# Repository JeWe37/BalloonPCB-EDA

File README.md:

# BalloonPCB-EDA

KiCAD EDA Files for the Balloon PCB.

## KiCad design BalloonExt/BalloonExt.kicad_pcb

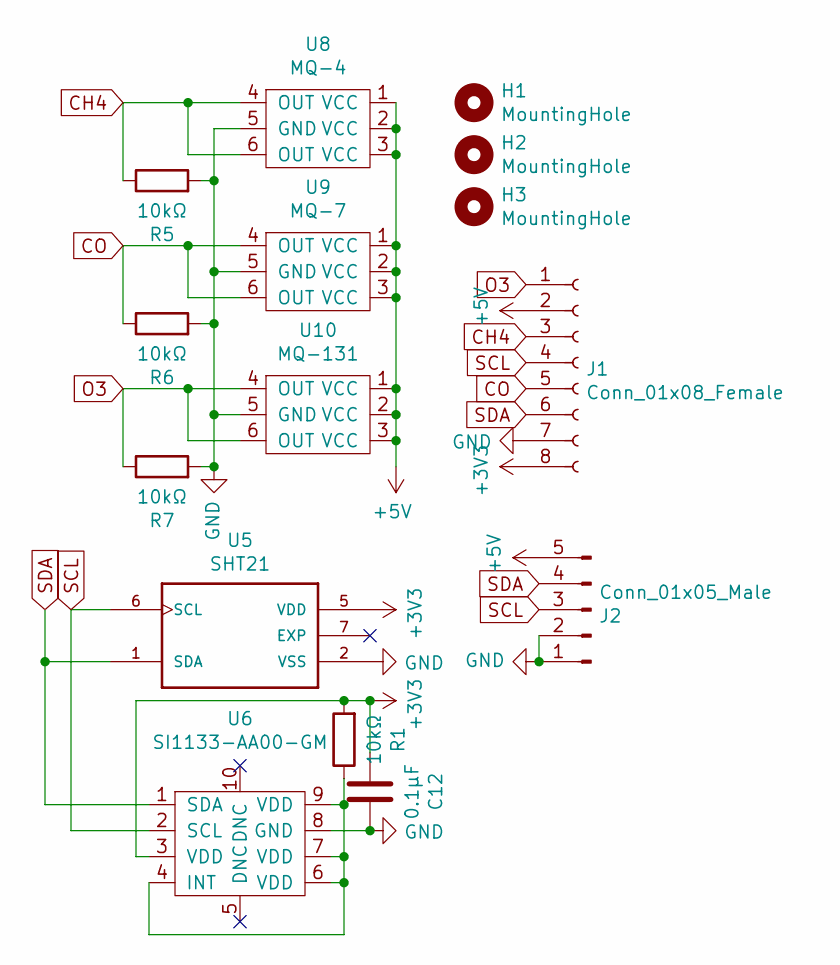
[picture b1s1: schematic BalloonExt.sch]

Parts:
C12: 0.1µF; C_0805_2012Metric
H1, H2, H3: MountingHole; MountingSlot_2.7x1mm
J1: Conn_01x08_Female; PinHeader_2x04_P1.27mm_Vertical
J2: Conn_01x05_Male; B5B-ZR
R1, R5, R6, R7: 10kΩ; R_0805_2012Metric
U5: SHT21; SON100P300X300X110-7N
U6: SI1133-AA00-GM; si1132
U8: MQ-4; mq-4
U9: MQ-7; mq-7
U10: MQ-131; mq-131

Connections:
+3V3: C12.2, J1.8, R1.2, U5.5 (VDD), U6.3 (VDD)
+5V: J1.2, J2.5, U8.1 (VCC), U8.2 (VCC), U8.3 (VCC), U9.1 (VCC), U9.2 (VCC), U9.3 (VCC), U10.1 (VCC), U10.2 (VCC), U10.3 (VCC)
CH4: J1.3, R5.1, U8.4 (OUT), U8.6 (OUT)
CO: J1.5, R6.1, U9.4 (OUT), U9.6 (OUT)
GND: C12.1, J1.7, J2.1, J2.2, R5.2, R6.2, R7.2, U5.2 (VSS), U6.8 (GND), U8.5 (GND), U9.5 (GND), U10.5 (GND)
unnamed: R1.1, U6.4 (INT), U6.6 (VDD), U6.7 (VDD), U6.9 (VDD)
O3: J1.1, R7.1, U10.4 (OUT), U10.6 (OUT)
SCL: J1.4, J2.3, U5.6 (SCL), U6.2 (SCL)
SDA: J1.6, J2.4, U5.1 (SDA), U6.1 (SDA)

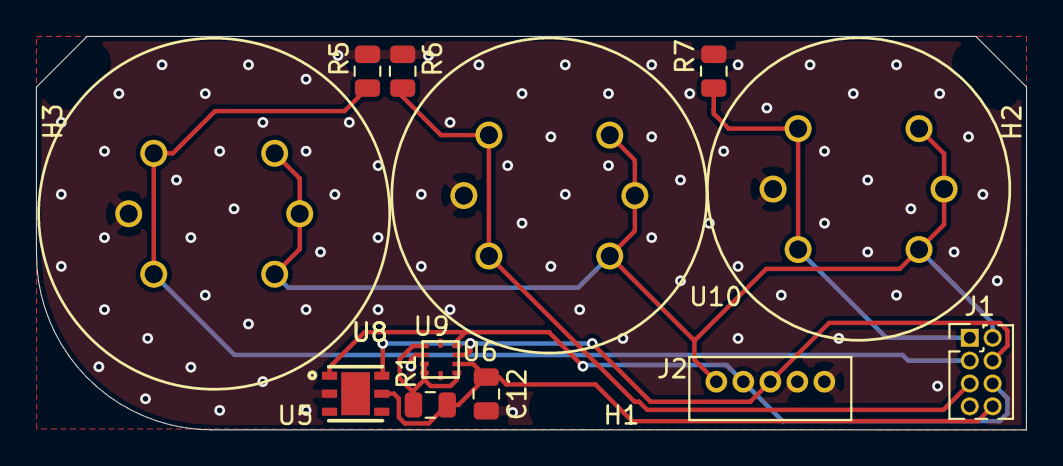
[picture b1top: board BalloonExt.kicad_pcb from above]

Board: 2 copper layers, 55.0 x 21.9 mm, 15 parts (0 on the bottom side), 9 nets.

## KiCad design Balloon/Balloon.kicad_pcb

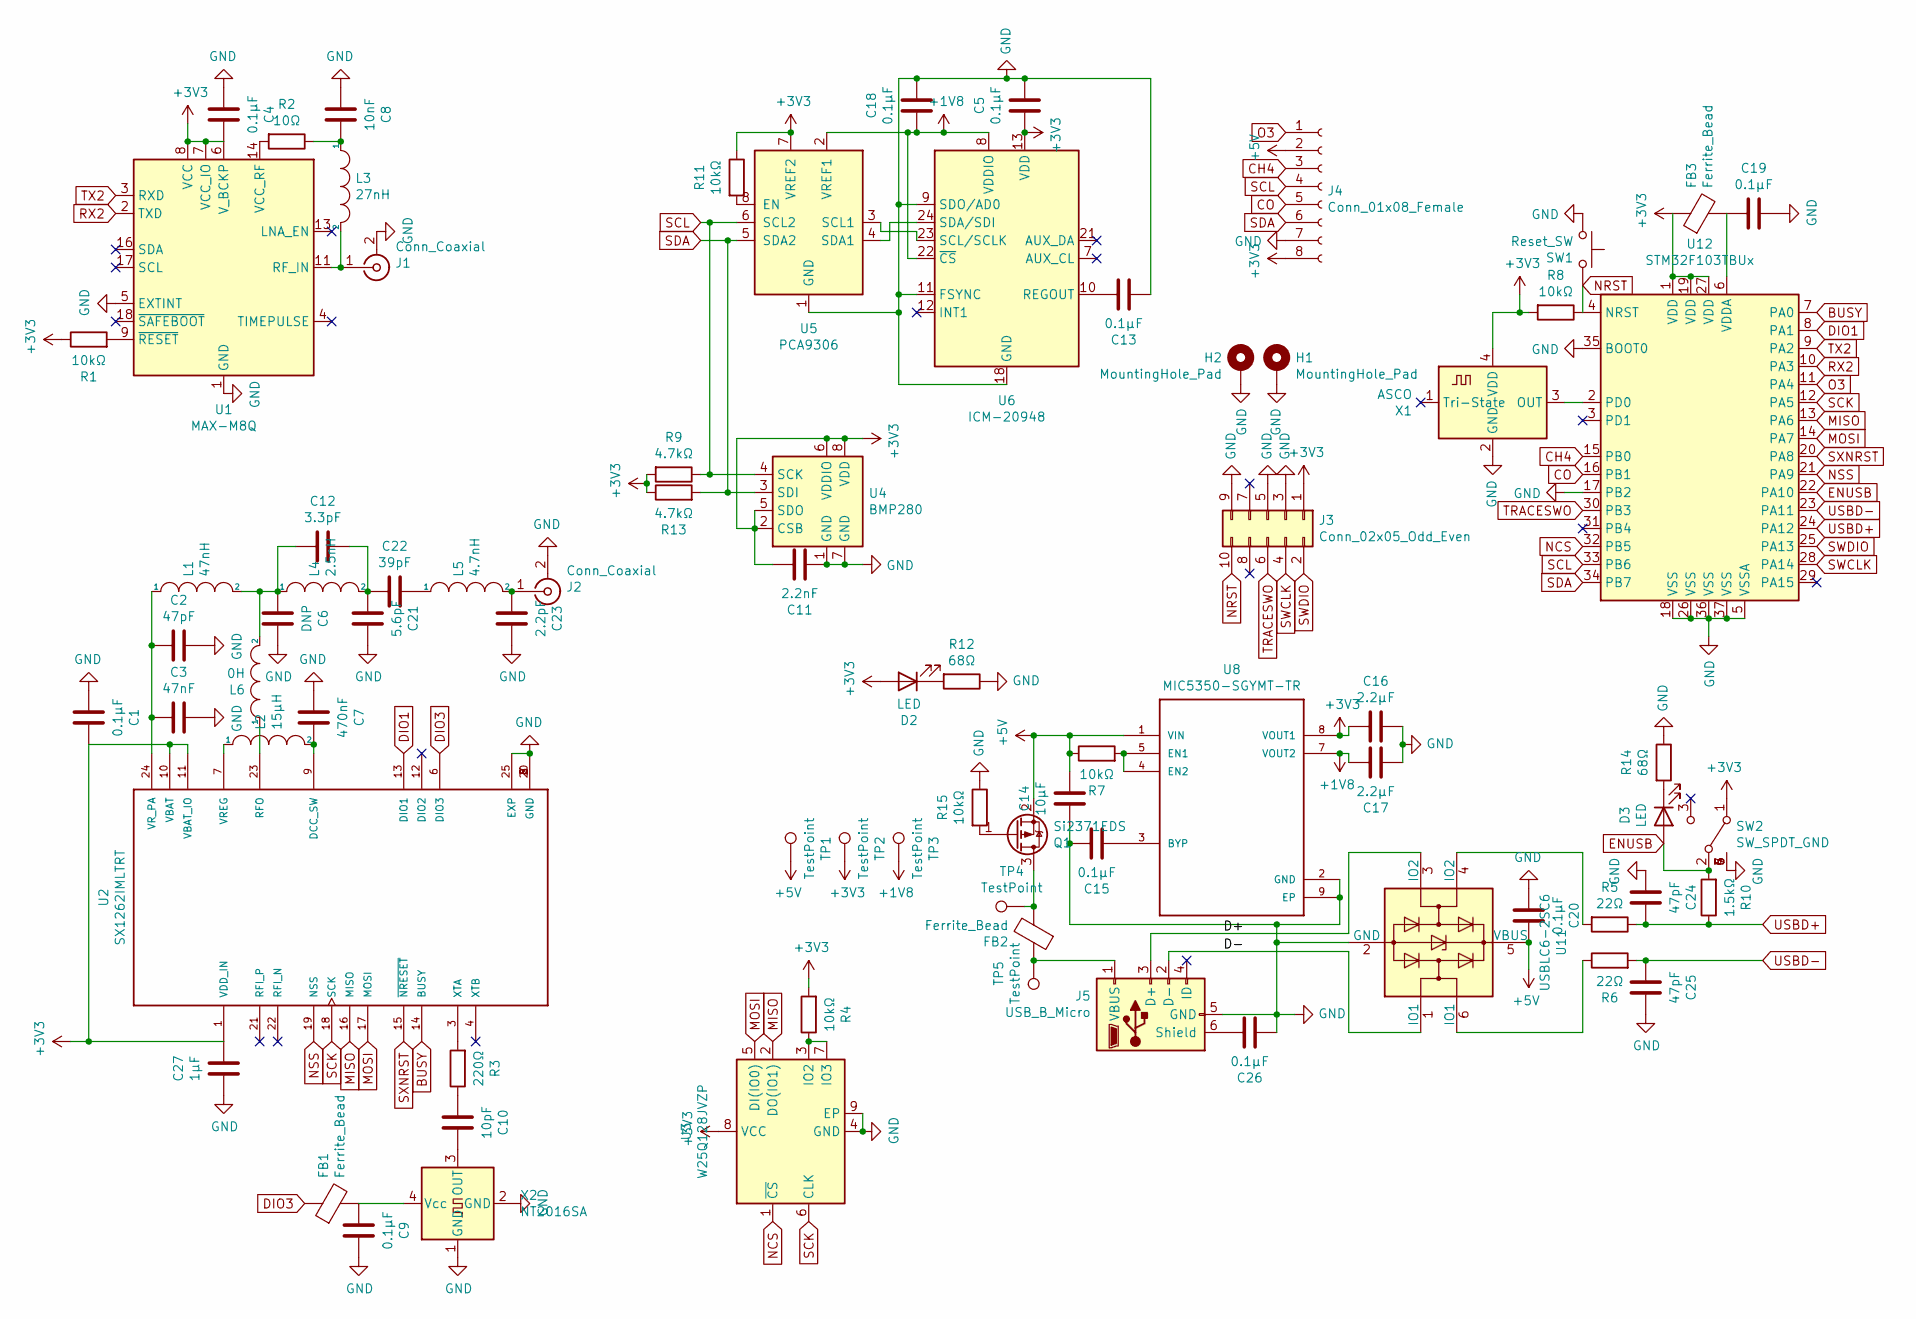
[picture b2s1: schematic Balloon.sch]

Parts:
C1, C4, C5, C9, C13, C15, C18, C19, C20, C26: 0.1µF; C_0201_0603Metric
C2, C24, C25: 47pF; C_0201_0603Metric
C3: 47nF; C_0201_0603Metric
C6: DNP; C_0201_0603Metric
C7: 470nF; C_0201_0603Metric
C8: 10nF; C_0201_0603Metric
C10: 10pF; C_0201_0603Metric
C11: 2.2nF; C_0201_0603Metric
C12: 3.3pF; C_0201_0603Metric
C14: 10µF; C_0603_1608Metric
C16, C17: 2.2µF; C_0402_1005Metric
C21: 5.6pF; C_0201_0603Metric
C22: 39pF; C_0201_0603Metric
C23: 2.2pF; C_0201_0603Metric
C27: 1µF; C_0402_1005Metric
D2, D3: LED; LED_0603_1608Metric
FB1, FB2, FB3: Ferrite_Bead; L_0402_1005Metric
H1, H2: MountingHole_Pad; MountingHole_2.2mm_M2_DIN965_Pad
J1: Conn_Coaxial; U.FL_Molex_MCRF_73412-0110_Vertical
J2: Conn_Coaxial; SMA_Amphenol_132289_EdgeMount
J3: Conn_02x05_Odd_Even; PinHeader_2x05_P1.27mm_Vertical
J4: Conn_01x08_Female; PinHeader_2x04_P1.27mm_Vertical
J5: USB_B_Micro; USB_Micro-B_Wuerth_629105150521
L1: 47nH; L_0201_0603Metric
L2: 15µH; L_0805_2021Metric_TDK
L3: 27nH; L_0201_0603Metric
L4: 2.5nH; L_0201_0603Metric
L5: 4.7nH; L_0201_0603Metric
L6: 0H; L_0201_0603Metric
Q1: Si2371EDS; SOT-23
R1, R4, R7, R8, R11, R15: 10kΩ; R_0201_0603Metric
R2: 10Ω; R_0201_0603Metric
R3: 220Ω; R_0201_0603Metric
R5, R6: 22Ω; R_0201_0603Metric
R9, R13: 4.7kΩ; R_0201_0603Metric
R10: 1.5kΩ; R_0201_0603Metric
R12, R14: 68Ω; R_0201_0603Metric
SW1: Reset_SW; SW_SPST_SKQG_WithStem
SW2: SW_SPDT_GND; SSSS811101
TP1, TP2, TP3, TP4, TP5: TestPoint; TestPoint_Pad_D2.5mm
U1: MAX-M8Q; ublox_MAX
U2: SX1262IMLTRT; QFN50P400X400X100-25N
U3: W25Q128JVZP; WSON-8-1EP_6x5mm_P1.27mm_EP3.4x4.3mm
U4: BMP280; Bosch_LGA-8_2x2.5mm_P0.65mm_ClockwisePinNumbering
U5: PCA9306; UQFN-8_1.6x1.6mm_P0.5mm
U6: ICM-20948; InvenSense_QFN-24_3x3mm_P0.4mm
U8: MIC5350-SGYMT-TR; SON50P200X200X60-9N
U11: USBLC6-2SC6; SOT-666
U12: STM32F103TBUx; QFN-36-1EP_6x6mm_P0.5mm_EP4.1x4.1mm
X1: ASCO; Oscillator_SMD_Abracon_ASCO-4Pin_1.6x1.2mm
X2: NT2016SA; SOIC254P1016X440-4N

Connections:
+1V8: C17.2, C18.2, TP3.1, U5.2 (VREF1), U6.8 (VDDIO), U6.22 (~CS), U8.7 (VOUT2); also elsewhere on the board
+5V: C14.1, C20.1, J4.2, Q1.2 (S), R7.1, TP1.1, U8.1 (VIN), U11.5 (VBUS); also elsewhere on the board
/D+: J5.3 (D+), U11.3 (IO2)
/D-: J5.2 (D-), U11.1 (IO1)
BUSY: U2.14 (BUSY), U12.7 (PA0)
CH4: J4.3, U12.15 (PB0)
CO: J4.5, U12.16 (PB1)
DIO1: U2.13 (DIO1), U12.8 (PA1)
DIO3: FB1.1, U2.6 (DIO3)
ENUSB: D3.2 (A), R10.2, SW2.2 (B), U12.22 (PA10)
MISO: U2.16 (MISO), U3.2 (DO(IO1)), U12.13 (PA6)
MOSI: U2.17 (MOSI), U3.5 (DI(IO0)), U12.14 (PA7)
NCS: U3.1 (~CS), U12.32 (PB5)
NRST: J3.10, R8.1, SW1.2, U12.4 (NRST)
NSS: U2.19 (NSS), U12.21 (PA9)
unnamed: C2.1, C3.1, L1.1, U2.24 (VR_PA)
unnamed: C7.1, L2.2, U2.9 (DCC_SW)
unnamed: C8.1, L3.1, R2.1
unnamed: C9.2, FB1.2, X2.4 (Vcc)
unnamed: C10.1, X2.3 (OUT)
unnamed: C10.2, R3.1
unnamed: C6.1, C12.1, L1.2, L4.1, L6.2
unnamed: C12.2, C21.1, C22.1, L4.2
unnamed: C13.1, U6.10 (REGOUT)
unnamed: C15.2, U8.3 (BYP)
unnamed: C19.2, FB3.2, U12.6 (VDDA)
unnamed: C22.2, L5.1
unnamed: C23.1, J2.1 (In), L5.2
unnamed: C26.1, J5.6 (Shield)
unnamed: D2.1 (K), R12.2
unnamed: D3.1 (K), R14.2
unnamed 31: FB2.1, J5.1 (VBUS), TP5.1; also elsewhere on the board
unnamed 32: FB2.2, Q1.3 (D), TP4.1; also elsewhere on the board
unnamed: J1.1 (In), L3.2, U1.11 (RF_IN)
unnamed: L2.1, U2.7 (VREG)
unnamed: L6.1, U2.23 (RFO)
unnamed: Q1.1 (G), R15.2
unnamed: R1.2, U1.9 (~RESET)
unnamed: R2.2, U1.14 (VCC_RF)
unnamed: R3.2, U2.3 (XTA)
unnamed: R4.1, U3.3 (IO2), U3.7 (IO3)
unnamed: R5.2, U11.4 (IO2)
unnamed: R6.1, U11.6 (IO1)
unnamed: R7.2, U8.4 (EN2), U8.5 (EN1)
unnamed: R11.2, U5.8 (EN)
unnamed: U5.3 (SCL1), U6.23 (SCL/SCLK)
unnamed: U5.4 (SDA1), U6.24 (SDA/SDI)
unnamed: U12.2 (PD0), X1.3 (OUT)
O3: J4.1, U12.11 (PA4)
RX2: U1.2 (TXD), U12.10 (PA3)
SCK: U2.18 (SCK), U3.6 (CLK), U12.12 (PA5)
SCL: J4.4, R9.1, U4.4 (SCK), U5.6 (SCL2), U12.33 (PB6)
SWCLK: J3.4, U12.28 (PA14)
SWDIO: J3.2, U12.25 (PA13)
SXNRST: U2.15 (~NRESET~), U12.20 (PA8)
TRACESWO: J3.6, U12.30 (PB3)
TX2: U1.3 (RXD), U12.9 (PA2)
USBD+: C24.1, R5.1, R10.1, U12.24 (PA12)
USBD-: C25.2, R6.2, U12.23 (PA11)

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
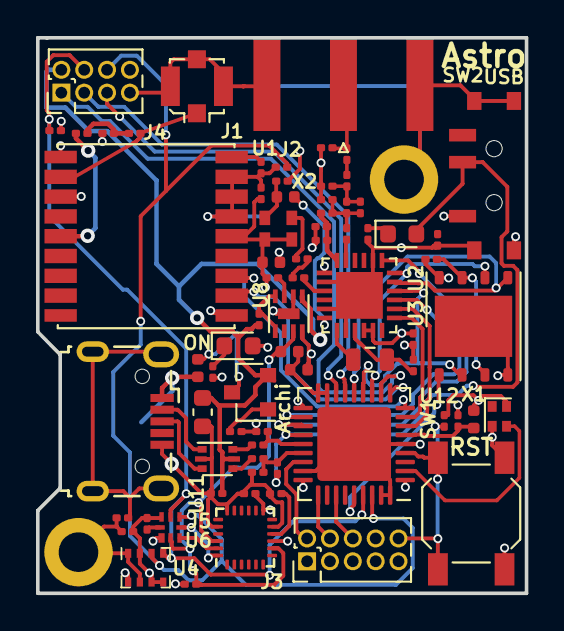
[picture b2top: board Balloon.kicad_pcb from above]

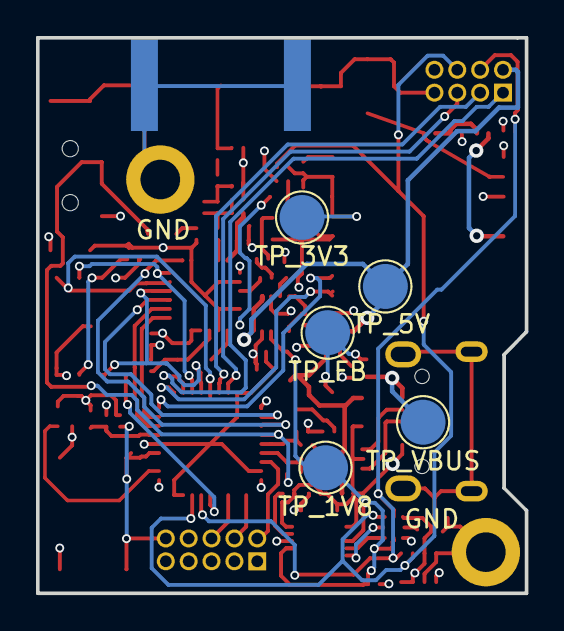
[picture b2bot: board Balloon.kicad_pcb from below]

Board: 4 copper layers, 27.2 x 30.9 mm, 80 parts (5 on the bottom side), 62 nets.

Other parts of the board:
R13#2: 4.7kΩ; R_0201_0603Metric
TP_1V8, TP_3V3, TP_5V: TestPoint; TestPoint_Pad_D2.5mm
TP_FB: TestPoint; TestPoint_Pad_D2.5mm
TP_VBUS: TestPoint; TestPoint_Pad_D2.5mm

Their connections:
+1V8: TP_1V8.1; also elsewhere on the board
+5V: TP_5V.1; also elsewhere on the board
unnamed 31: TP_VBUS.1; also elsewhere on the board
unnamed 32: TP_FB.1; also elsewhere on the board
